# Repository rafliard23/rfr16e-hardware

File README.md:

# rfr16e-hardware

Hardware and schematics of My RFR16E Macropad

Uses STM32F401CCU6 "WeAct BlackPill" as MCU.

© 2021 Muhammad Rafli Ardiansyah

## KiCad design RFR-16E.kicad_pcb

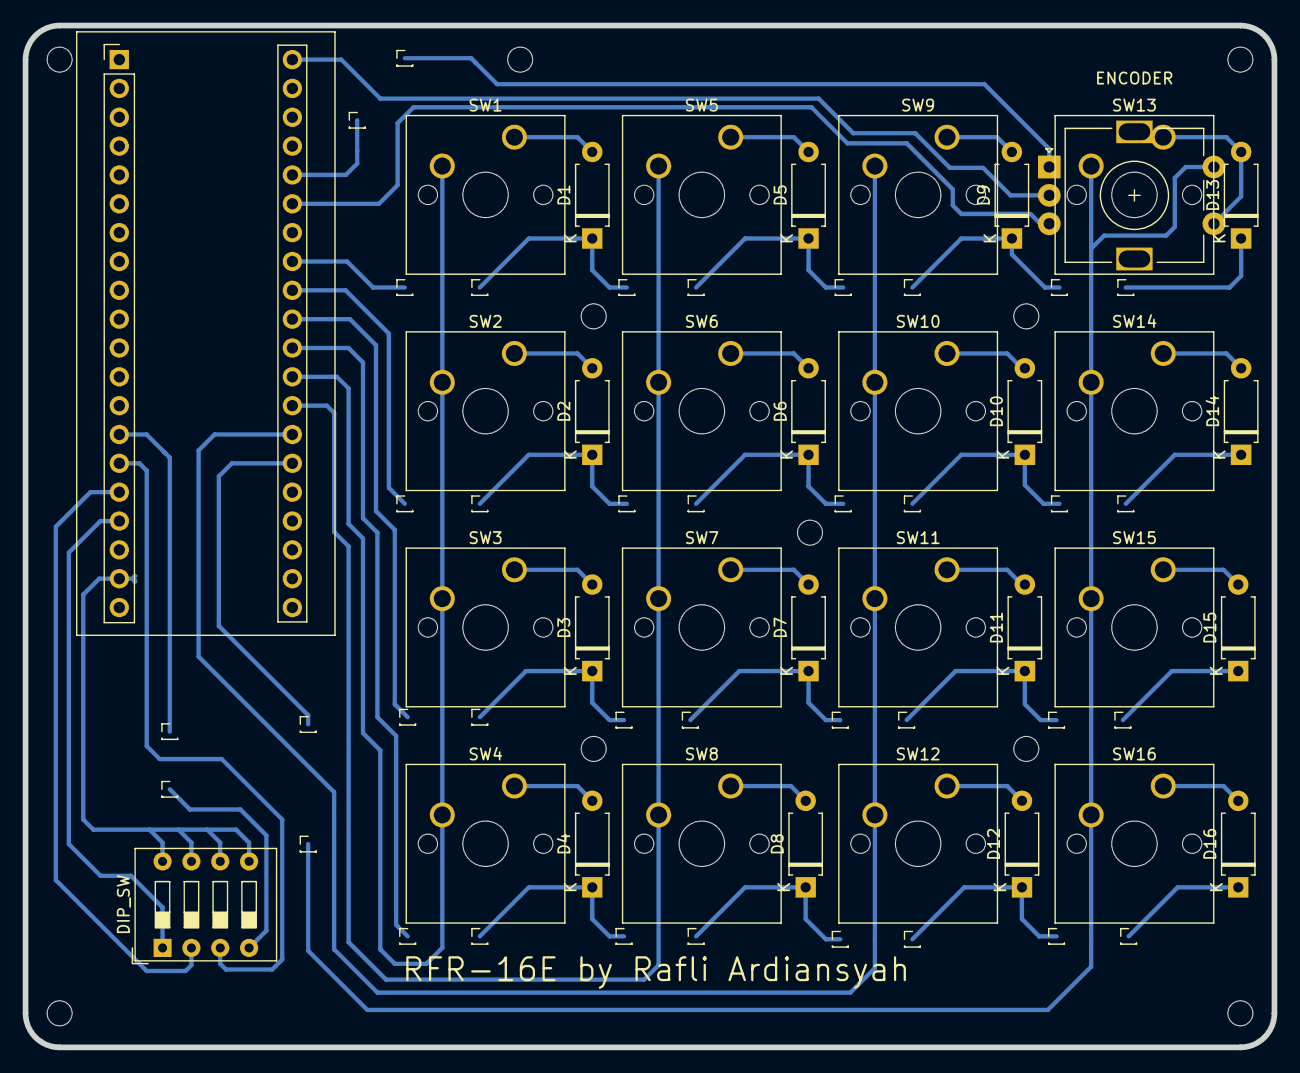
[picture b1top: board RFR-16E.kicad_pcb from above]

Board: 2 copper layers, 110.0 x 90.0 mm, 35 parts (0 on the bottom side), 32 nets.

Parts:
D1, D2, D3, D4, D5, D6, D7, D8, D9, D10, D11, D12, D13, D14, D15, D16: D_Small_ALT; D_A-405_P7.62mm_Horizontal
DIP_SW: SW_DIP_x04; SW_DIP_SPSTx04_Slide_9.78x12.34mm_W7.62mm_P2.54mm
ENCODER: Rotary_Encoder_Switch; RotaryEncoder_Alps_EC11E-Switch_Vertical_H20mm
SW1, SW2, SW3, SW4, SW5, SW6, SW7, SW8, SW9, SW10, SW11, SW12, SW13, SW14, SW15, SW16: SW_SPST; SW_Cherry_MX_1.00u_PCB
U1: YAAJ_BluePill_Part_Like; YAAJ_BluePill_2

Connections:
A_E: ENCODER.A, U1.36
B_E: ENCODER.B, U1.35
GND: DIP_SW.5, DIP_SW.6, DIP_SW.7, DIP_SW.8, U1.19
GND_E: ENCODER.C, U1.40
unnamed: D1.2, SW1.1
unnamed: D2.2, SW2.1
unnamed: D3.2, SW3.1
unnamed: D4.2, SW4.1
unnamed: D5.2, SW5.1
unnamed: D6.2, SW6.1
unnamed: D7.2, SW7.1
unnamed: D8.2, SW8.1
unnamed: D9.2, SW9.1
unnamed: D10.2, SW10.1
unnamed: D11.2, SW11.1
unnamed: D12.2, SW12.1
unnamed: D13.2, ENCODER.S1, SW13.1
unnamed: D14.2, SW14.1
unnamed: D15.2, SW15.1
unnamed: D16.2, SW16.1
baris1: D1.1, D5.1, D9.1, D13.1, U1.33
baris2: D2.1, D6.1, D10.1, D14.1, U1.32
baris3: D3.1, D7.1, D11.1, D15.1, U1.31
baris4: D4.1, D8.1, D12.1, D16.1, U1.30
kolom1: SW1.2, SW2.2, SW3.2, SW4.2, U1.29
kolom2: SW5.2, SW6.2, SW7.2, SW8.2, U1.28
kolom3: SW9.2, SW10.2, SW11.2, SW12.2, U1.27
kolom4: ENCODER.S2, SW13.2, SW14.2, SW15.2, SW16.2, U1.26
sw_ch1: DIP_SW.1, U1.17
sw_ch2: DIP_SW.2, U1.16
sw_ch3: DIP_SW.3, U1.15
sw_ch4: DIP_SW.4, U1.14

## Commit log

2023-06-09 Uploaded files
    Added schematics, board and images
2023-06-09 fixed image
